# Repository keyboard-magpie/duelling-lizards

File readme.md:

A split 36 key ergo, which uses one elite c/goldfish/comet (pro micro won't work!), and two midi cables (5 pin din), to work.

Also has a breakout for an ADNS sensor, because why not.

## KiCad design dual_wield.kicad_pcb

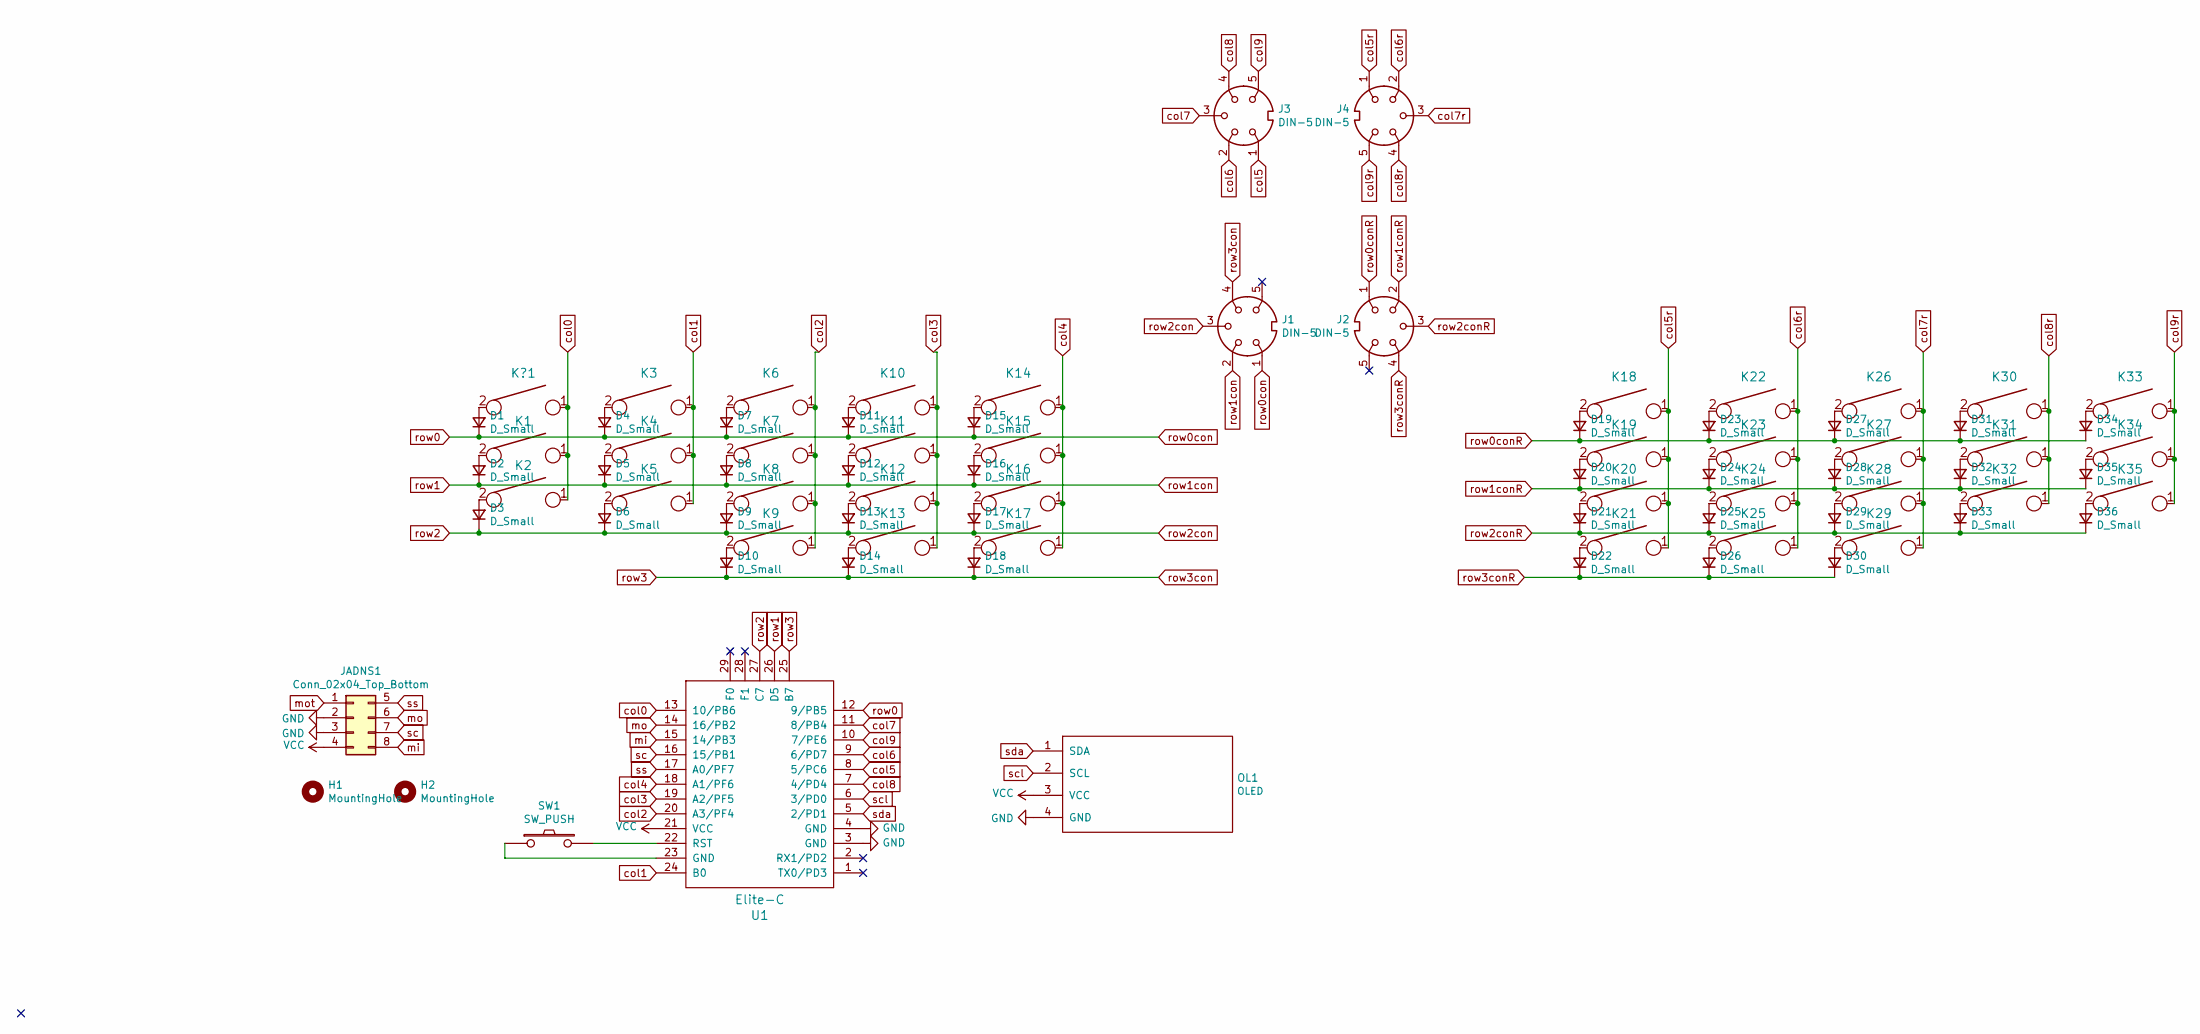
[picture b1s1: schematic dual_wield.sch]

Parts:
D1, D2, D3, D4, D5, D6, D7, D8, D9, D10, D11, D12, D13, D14, D15, D16, D17, D18, D19, D20, D21, D22, D23, D24, D25, D26, D27, D28, D29, D30, D31, D32, D33, D34, D35, D36: D_Small; D_SOD123
H1, H2: MountingHole; MountingHole_3.2mm_M3
J1, J2, J3, J4: DIN-5; CUI_SDS-50J
JADNS1: Conn_02x04_Top_Bottom; PinHeader_2x04_P2.54mm_Horizontal
K1, K2, K3, K4, K5, K6, K7, K8, K9, K10, K11, K12, K13, K14, K15, K16, K17, K18, K19, K20, K21, K22, K23, K24, K25, K26, K27, K28, K29, K30, K31, K32, K33, K34, K35: KEYSW; Kailh-PG1350-1u-NoLED
K?1: KEYSW; Kailh-PG1350-1u-NoLED
OL1: OLED
SW1: SW_PUSH; ResetSW_1side
U1: Elite-C; Elite-C-ZigZag

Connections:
GND: JADNS1.2, JADNS1.3, OL1.4 (GND), U1.3 (GND), U1.4 (GND)
unnamed: D1.2 (A), K?1.2
unnamed: D2.2 (A), K1.2
unnamed: D3.2 (A), K2.2
unnamed: D4.2 (A), K3.2
unnamed: D5.2 (A), K4.2
unnamed: D6.2 (A), K5.2
unnamed: D7.2 (A), K6.2
unnamed: D8.2 (A), K7.2
unnamed: D9.2 (A), K8.2
unnamed: D10.2 (A), K9.2
unnamed: D11.2 (A), K10.2
unnamed: D12.2 (A), K11.2
unnamed: D13.2 (A), K12.2
unnamed: D14.2 (A), K13.2
unnamed: D15.2 (A), K14.2
unnamed: D16.2 (A), K15.2
unnamed: D17.2 (A), K16.2
unnamed: D18.2 (A), K17.2
unnamed: D19.2 (A), K18.2
unnamed: D20.2 (A), K19.2
unnamed: D21.2 (A), K20.2
unnamed: D22.2 (A), K21.2
unnamed: D23.2 (A), K22.2
unnamed: D24.2 (A), K23.2
unnamed: D25.2 (A), K24.2
unnamed: D26.2 (A), K25.2
unnamed: D27.2 (A), K26.2
unnamed: D28.2 (A), K27.2
unnamed: D29.2 (A), K28.2
unnamed: D30.2 (A), K29.2
unnamed: D31.2 (A), K30.2
unnamed: D32.2 (A), K31.2
unnamed: D33.2 (A), K32.2
unnamed: D34.2 (A), K33.2
unnamed: D35.2 (A), K34.2
unnamed: D36.2 (A), K35.2
unnamed: SW1.1, U1.23 (GND)
unnamed: SW1.2, U1.22 (RST)
VCC: JADNS1.4, OL1.3 (VCC), U1.21 (VCC)
col0: K1.1, K2.1, K?1.1, U1.13 (10/PB6)
col1: K3.1, K4.1, K5.1, U1.24 (B0)
col2: K6.1, K7.1, K8.1, K9.1, U1.20 (A3/PF4)
col3: K10.1, K11.1, K12.1, K13.1, U1.19 (A2/PF5)
col4: K14.1, K15.1, K16.1, K17.1, U1.18 (A1/PF6)
col5: J3.1, U1.8 (5/PC6)
col5r: J4.1, K18.1, K19.1, K20.1, K21.1
col6: J3.2, U1.9 (6/PD7)
col6r: J4.2, K22.1, K23.1, K24.1, K25.1
col7: J3.3, U1.11 (8/PB4)
col7r: J4.3, K26.1, K27.1, K28.1, K29.1
col8: J3.4, U1.7 (4/PD4)
col8r: J4.4, K30.1, K31.1, K32.1
col9: J3.5, U1.10 (7/PE6)
col9r: J4.5, K33.1, K34.1, K35.1
mi: JADNS1.8, U1.15 (14/PB3)
mo: JADNS1.6, U1.14 (16/PB2)
mot: JADNS1.1
row0: D1.1 (K), D4.1 (K), D7.1 (K), D11.1 (K), D15.1 (K), J1.1, U1.12 (9/PB5)
row0conR: D19.1 (K), D23.1 (K), D27.1 (K), D31.1 (K), D34.1 (K), J2.1
row1: D2.1 (K), D5.1 (K), D8.1 (K), D12.1 (K), D16.1 (K), J1.2, U1.26 (D5)
row1conR: D20.1 (K), D24.1 (K), D28.1 (K), D32.1 (K), D35.1 (K), J2.2
row2: D3.1 (K), D6.1 (K), D9.1 (K), D13.1 (K), D17.1 (K), J1.3, U1.27 (C7)
row2conR: D21.1 (K), D25.1 (K), D29.1 (K), D33.1 (K), D36.1 (K), J2.3
row3: D10.1 (K), D14.1 (K), D18.1 (K), J1.4, U1.25 (B7)
row3conR: D22.1 (K), D26.1 (K), D30.1 (K), J2.4
sc: JADNS1.7, U1.16 (15/PB1)
scl: OL1.2 (SCL), U1.6 (3/PD0)
sda: OL1.1 (SDA), U1.5 (2/PD1)
ss: JADNS1.5, U1.17 (A0/PF7)

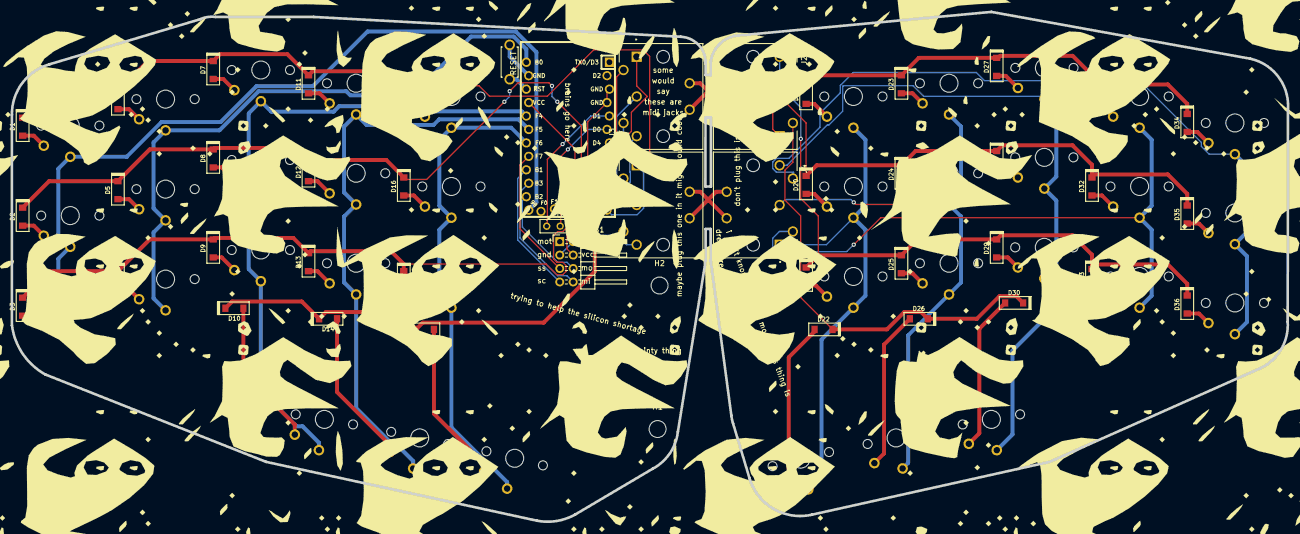
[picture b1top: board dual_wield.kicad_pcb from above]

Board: 2 copper layers, 241.1 x 96.3 mm, 82 parts (1 on the bottom side), 69 nets.

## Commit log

2021-06-06 initial
2021-06-06 tidy
2021-06-06 Create LICENSE
